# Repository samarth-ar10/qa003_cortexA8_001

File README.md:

# aq003_cortexA8 [ on HOLD ]
cortexA8 based system for qa003 to display and provide additional fire power!!

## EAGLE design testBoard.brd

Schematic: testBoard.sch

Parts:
C1, C6, C9, C12, C15, C18: 0.01uf; C0805
C2, C7, C10, C13, C16, C19: 1uf; C0805
C3, C8, C11, C14, C17, C20: 10uf; C0805
C4, C5: 0.1uf; C0805
D1, D2, D3, D4, D5, D6, D7, D8, D9, D10, D11, D12: 1n4002; DO-214AC
DISPLAY_POWER: PINHD-1X2; 1X02
IC1: AM3358BZCZ100; BGA324C80P18X18_1500X1500X140
IC2, IC3, IC4, IC5, IC6, IC7: LM317MABDT; DPACK
J1: 1040310811
J2: 54104-4031
J3: 200529-0040; 2005290040
J4: M50-3610542R; M503610542
JP1, JP2, JP3: PINHD-1X4; 1X04
PS1, PS2, PS3, PS4: PINHD-1X2; 1X02
R1, R5, R9, R10, R13, R16, R17: 10ohm; R0805W
R2: 30ohm; R0805W
R6, R7, R15: 100ohm; R0805W
R8, R11: 1kohm; R0805W
R12: 3.3kohm; R0805W
R14, R19: 470ohm; R0805W
R18, R21, R23: 246ohm; R0805W
R20, R22, R24: 150ohm; R0805W
U$1: IS42S1610G-5BL; TF-BGA54

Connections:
DDR_A0: IC1.F3 (DDR_A0), U$1.H7 (H7-A0)
DDR_A1: IC1.H1 (DDR_A1), U$1.H8 (H8-A1)
DDR_A2: IC1.E4 (DDR_A2), U$1.J8 (J8-A2)
DDR_A3: IC1.C3 (DDR_A3), U$1.J7 (J7-A3)
DDR_A4: IC1.C2 (DDR_A4), U$1.J3 (J3-A4)
DDR_A5: IC1.B1 (DDR_A5), U$1.J2 (J2-A5)
DDR_A6: IC1.D5 (DDR_A6), U$1.H3 (H3-A6)
DDR_A7: IC1.E2 (DDR_A7), U$1.H2 (H2-A7)
DDR_A8: IC1.D4 (DDR_A8), U$1.H1 (H1-A8)
DDR_A9: IC1.C1 (DDR_A9), U$1.G3 (G3-A9)
DDR_A10: IC1.F4 (DDR_A10), U$1.H9 (H9-A10)
DDR_A11: IC1.F2 (DDR_A11), U$1.G2 (G2-A11)
DDR_A12: IC1.E3 (DDR_A12), U$1.G1 (G1-A12)
DDR_BA0: IC1.C4 (DOR_BA0), U$1.G7 (G7-BA0)
DDR_BA1: IC1.E1 (DDR_BA1), U$1.G8 (G8-BA1)
DDR_CASN: IC1.F1 (DDR_CASN), U$1.F7 (F7-CAS)
DDR_CK: IC1.D2 (DDR_CK), U$1.F2 (F2-CLK)
DDR_CKE: IC1.G3 (DDR_CKE), U$1.F3 (F3-CKE)
DDR_CSN0: IC1.H2 (DDR_CSNO), U$1.G9 (G9-CS)
DDR_D0: IC1.M3 (DDR_D0), U$1.A8 (A8-DQ0)
DDR_D1: IC1.M4 (DDR_D1), U$1.B9 (B9-DQ1)
DDR_D2: IC1.N1 (DDR_D2), U$1.B8 (B8-DQ2)
DDR_D3: IC1.N2 (DDR_D3), U$1.C9 (C9-DQ3)
DDR_D4: IC1.N3 (DDR_D4), U$1.C8 (C8-DQ4)
DDR_D5: IC1.N4 (DDR_D5), U$1.D9 (D9-DQ5)
DDR_D6: IC1.P3 (DDR_D6), U$1.D8 (D8-DQ6)
DDR_D7: IC1.P4 (DDR_D7), U$1.E9 (E9-DQ7)
DDR_D8: IC1.J1 (DDR_D8), U$1.E1 (E1-DQ8)
DDR_D9: IC1.K1 (DDR_D9), U$1.D2 (D2-DQ9)
DDR_D10: IC1.K2 (DDR_D10), U$1.D1 (D1-DQ10)
DDR_D11: IC1.K3 (DDR_D11), U$1.C2 (C2-DQ11)
DDR_D12: IC1.K4 (DDR_D12), U$1.C1 (C1-DQ12)
DDR_D13: IC1.L3 (DDR_D13), U$1.B2 (B2-DQ13)
DDR_D14: IC1.L4 (DDR_D14), U$1.B1 (B1-DQ14)
DDR_D15: IC1.M1 (DDR_D15), U$1.A2 (A2-DQ15)
DDR_DQM0: IC1.M2 (DDR_DQM0), U$1.E8 (E8-DQML)
DDR_DQM1: IC1.J2 (DDR_DQM1), U$1.F1 (F1-DQMH)
DDR_DQS0: IC1.P1 (DDR_DQS0)
DDR_DQSN0: IC1.P2 (DDR_DQSN0)
DDR_RASN: IC1.G4 (DDR_RASN), U$1.F8 (F8-RAS)
DDR_VREF: C4.1, IC1.J4 (DDR_VREF)
DDR_WEN: IC1.B2 (DDR_WEN), U$1.F9 (F9-WE)
DISPLAY_POWER: DISPLAY_POWER.2, J2.31
GND: C1.2, C2.2, C3.2, C5.1, C6.2, C7.2, C8.2, C9.2, C10.2, C11.2, C12.2, C13.2, C14.2, C15.2, C16.2, C17.2, C18.2, C19.2, C20.2, J1.6 (VSS), J2.1, J2.3, J2.29, J2.36, J4.3, J4.5, PS1.1, PS2.1, PS3.1, PS4.1, R2.1, R6.1, R7.1, R13.1, R17.1, R18.1, R21.1, R23.1, U$1.A1 (A1-VSS), U$1.E3 (E3-VSS), U$1.J1 (J1-VSS)
JTAG_TCK: IC1.A12 (TCK), J4.4
JTAG_TDI: IC1.B11 (TDI), J4.8
JTAG_TDO: IC1.A11 (TDO), J4.6
JTAG_TEST_RESET_NTRST: IC1.B10 (TRSTN), J4.9
JTAG_TMS: IC1.C11 (TMS), J4.2
LCD_AC_BIAS_EN: IC1.R6 (LCD_AC_BIAS_EN), J2.34
LCD_DATA0: IC1.R1 (LCD_DATA0), J2.8
LCD_DATA1: IC1.R2 (LCD_DATA1), J2.9
LCD_DATA2: IC1.R3 (LCD_DATA2), J2.10
LCD_DATA3: IC1.R4 (LCD_DATA3), J2.11
LCD_DATA4: IC1.T1 (LCD_DATA4), J2.12
LCD_DATA5: IC1.T2 (LCD_DATA5), J2.15
LCD_DATA6: IC1.T3 (LCD_DATA6), J2.16
LCD_DATA7: IC1.T4 (LCD_DATA7), J2.17
LCD_DATA8: IC1.U1 (LCD_DATA8), J2.18
LCD_DATA9: IC1.U2 (LCD_DATA9), J2.19
LCD_DATA10: IC1.U3 (LCD_DATA10), J2.20
LCD_DATA11: IC1.U4 (LCD_DATA11), J2.24
LCD_DATA12: IC1.V2 (LCD_DATA12), J2.25
LCD_DATA13: IC1.V3 (LCD_DATA13), J2.26
LCD_DATA14: IC1.V4 (LCD_DATA14), J2.27
LCD_DATA15: IC1.T5 (LCD_DATA15), J2.28
LCD_DATA16: IC1.U13 (GPMC_AD15), J2.7
LCD_DATA17: IC1.V13 (GPMC_AD14), J2.23
LCD_DATA18: IC1.R12 (GPMC_AD13), J2.6
LCD_DATA19: IC1.T12 (GPMC_AD12), J2.14
LCD_DATA20: IC1.U12 (GPMC_AD11), J2.22
LCD_DATA21: IC1.T11 (GPMC_AD10), J2.5
LCD_DATA22: IC1.T10 (GPMC_AD9), J2.13
LCD_DATA23: IC1.U10 (GPMC_AD8), J2.21
LCD_HSYNC: IC1.R5 (LCD_HSYNC), J2.32
LCD_MEMORY_CLK: IC1.V12 (GPMC_CLK)
LCD_PCLK: IC1.V5 (LCD_PCLK), J2.30
LCD_TOUCH_XLEFT: IC1.B6 (AIN0), J3.1
LCD_TOUCH_XRIGHT: IC1.C7 (AINI), J3.3
LCD_TOUCH_YDOWN: IC1.A7 (AIN3), J3.2
LCD_TOUCH_YUP: IC1.B7 (AIN2), J3.4
LCD_VSYNC: IC1.U5 (LCD_VSYNC), J2.33
unnamed: IC1.J3 (DDR_VTP), R6.2, R7.2
unnamed: C4.2, U$1.A7 (A7-VDDQ), U$1.B3 (B3-VDDQ), U$1.C7 (C7-VDDQ), U$1.D3 (D3-VDDQ)
unnamed: C5.2, U$1.A3 (A3-VSSQ), U$1.B7 (B7-VSSQ), U$1.C3 (C3-VSSQ), U$1.D7 (D7-VSSQ)
unnamed: C14.1, D7.A, IC5.1 (ADJ), R18.2, R20.1
unnamed: C17.1, D9.A, IC6.1 (ADJ), R21.2, R22.1
unnamed: C3.1, D2.A, IC3.1 (ADJ), R1.1, R2.2
unnamed: C20.1, D11.A, IC7.1 (ADJ), R23.2, R24.1
unnamed: R5.1, R12.1
unnamed: C8.1, D1.A, IC2.1 (ADJ), R8.1, R11.1, R12.2
unnamed: R5.2, R9.2
unnamed: R9.1, R10.1
unnamed: R10.2, R13.2
unnamed: C11.1, D5.A, IC4.1 (ADJ), R15.1, R19.2
unnamed: R14.1, R19.1
unnamed: R14.2, R16.2
unnamed: R16.1, R17.2
NRESET_IN_OUT_AM3358: IC1.A10 (WARMRSTN), J4.10
SD_CLK: IC1.G17 (MMC0_CLK), J1.5 (CLK)
SD_CMD: IC1.G18 (MMC0_CMD), J1.3 (CMD)
SD_D0: IC1.G16 (MMC0_DAT0), J1.7 (DAT0)
SD_D1: IC1.G15 (MMC0_DAT1), J1.8 (DAT1)
SD_D2: IC1.F18 (MMC0_DAT2), J1.1 (DAT2)
SD_D3: IC1.F17 (MMC0_DAT3), J1.2 (CD/DAT3)
VIN: C1.1, C6.1, C9.1, C12.1, C15.1, C18.1, D3.C, D4.C, D6.C, D8.C, D10.C, D12.C, IC2.3 (IN), IC3.3 (IN), IC4.3 (IN), IC5.3 (IN), IC6.3 (IN), IC7.3 (IN), PS1.2, PS2.2, PS3.2, PS4.2
VIN_3.3: C13.1, C16.1, C19.1, D7.C, D8.A, D9.C, D10.A, D11.C, D12.A, DISPLAY_POWER.1, IC5.4 (OUT), IC6.4 (OUT), IC7.4 (OUT), J1.4 (VDD), J2.4, J4.1, R20.2, R22.2, R24.2, U$1.A9 (A9-VDD), U$1.E7 (E7-VDD), U$1.J9 (J9-VDD)
VIN_5: C2.1, D2.C, D3.A, IC3.4 (OUT), R1.2
VIN_9.6: C7.1, D1.C, D4.A, IC2.4 (OUT), J2.2, R8.2, R11.2
VIN_12: C10.1, D5.C, D6.A, IC4.4 (OUT), R15.2

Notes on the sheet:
processor AM3358BZCZ100
5V Voltage Regulator
5V, 1500mA
3V to 40V DC
Vref = 1.25V
5v power supply
memory IS42S16160G
storage MOLEX 1040310811
3.3v power supply
TFT DISPLAY NHD-7.0-800480EF-ASXV#-T
GPIO
Led
9.6v power supply
12v power supply
3.3V, 500mA
debugger

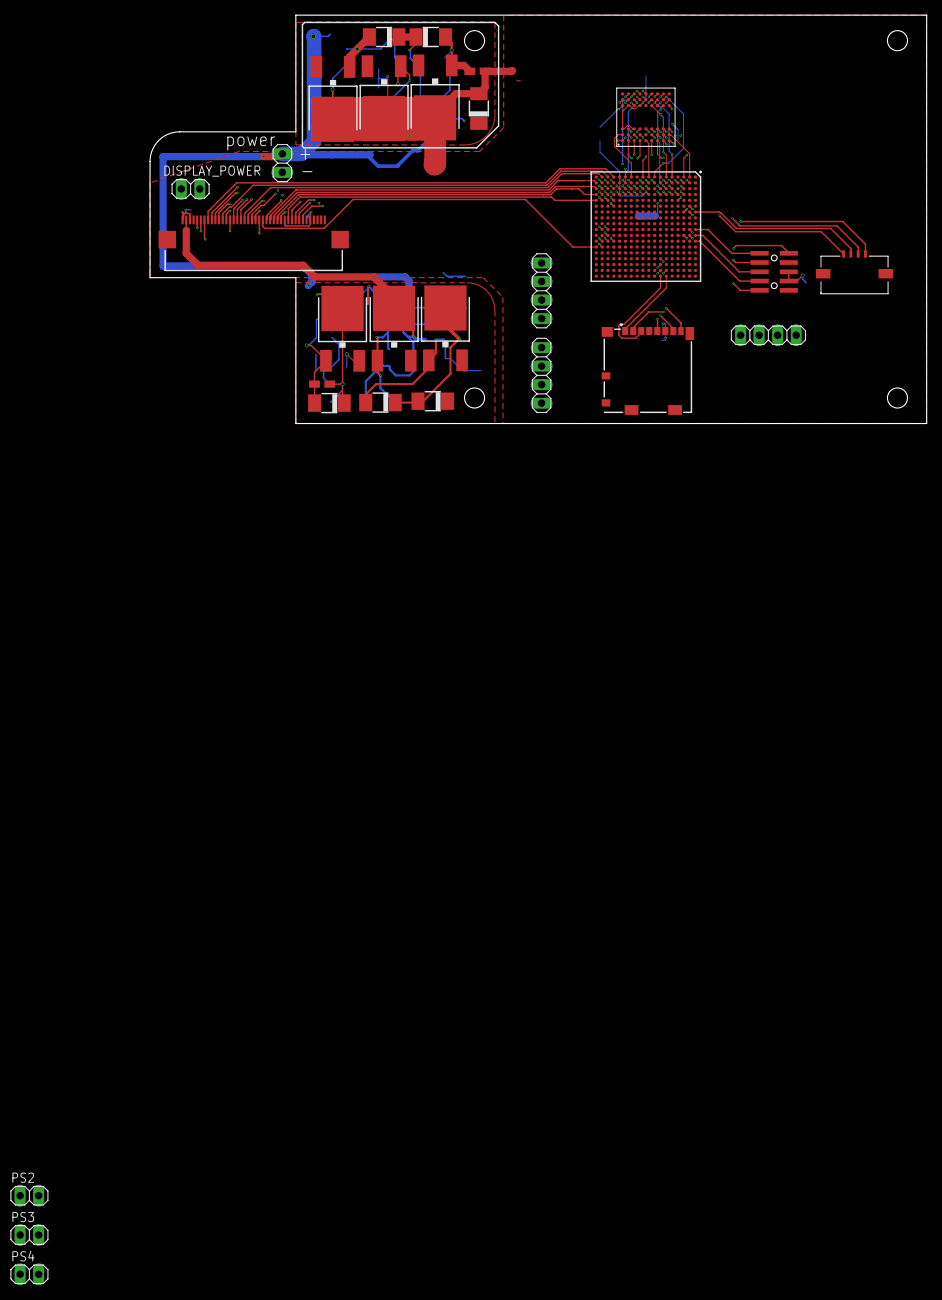
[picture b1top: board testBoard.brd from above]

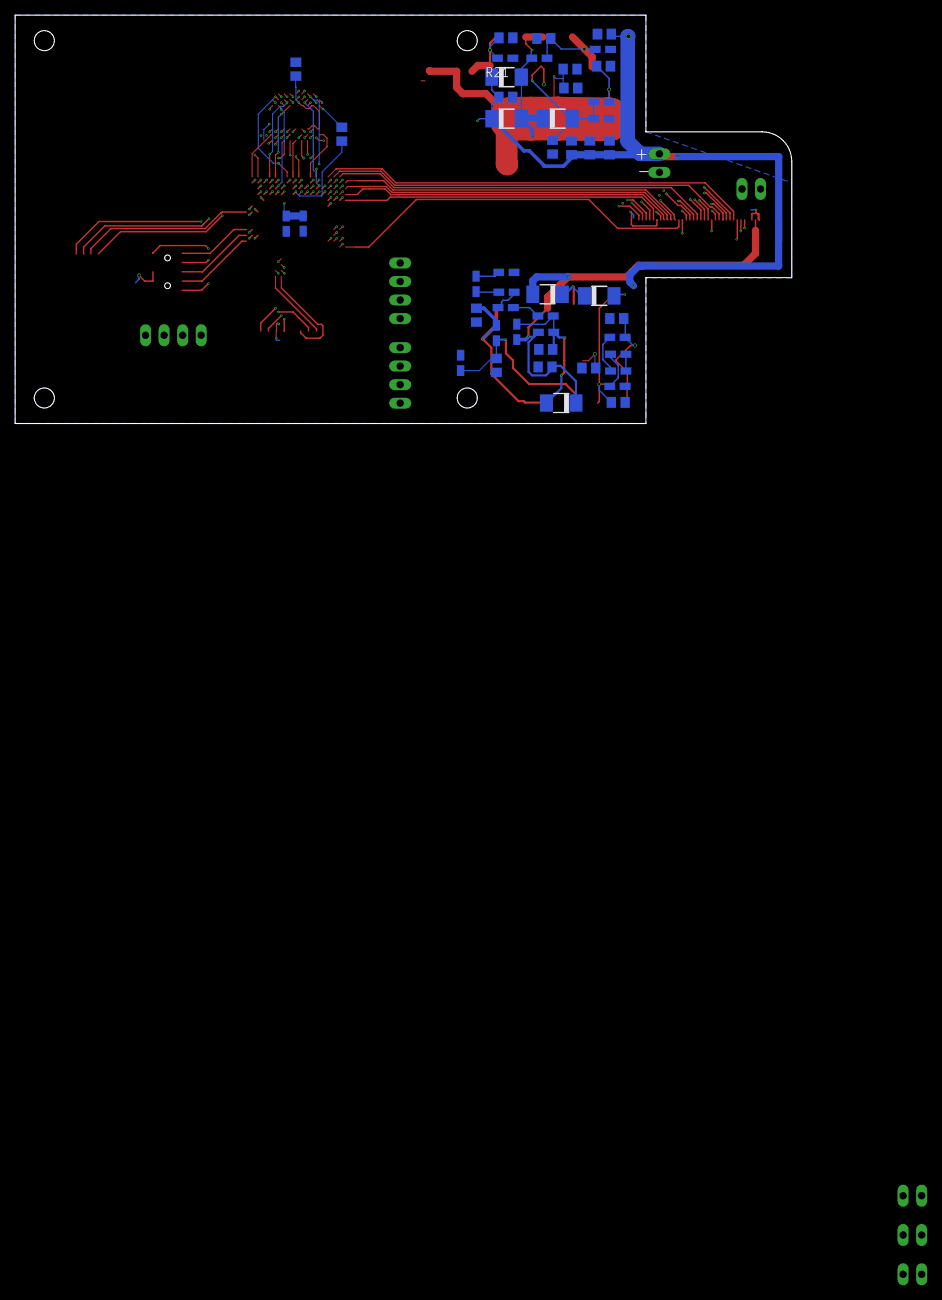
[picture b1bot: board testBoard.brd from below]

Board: 4 copper layers, 106.5 x 56.0 mm, 74 parts (46 on the bottom side), 107 nets.

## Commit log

2019-12-19 moving project from local testing to qa003 development
2019-12-21 syncing edit
2020-02-04 preparing to branch out for edit
    need to edit for accommodating track width of more than or equal to 1.25mm
2020-02-16 Completed schematic for prototype 001
2020-02-23 checkpoint
2020-02-24 sync checkpoint
2020-02-29 final submit for SAMARTH
2020-03-01 Cleaning
2020-03-15 Create Photos
2020-03-15 Adding Images
